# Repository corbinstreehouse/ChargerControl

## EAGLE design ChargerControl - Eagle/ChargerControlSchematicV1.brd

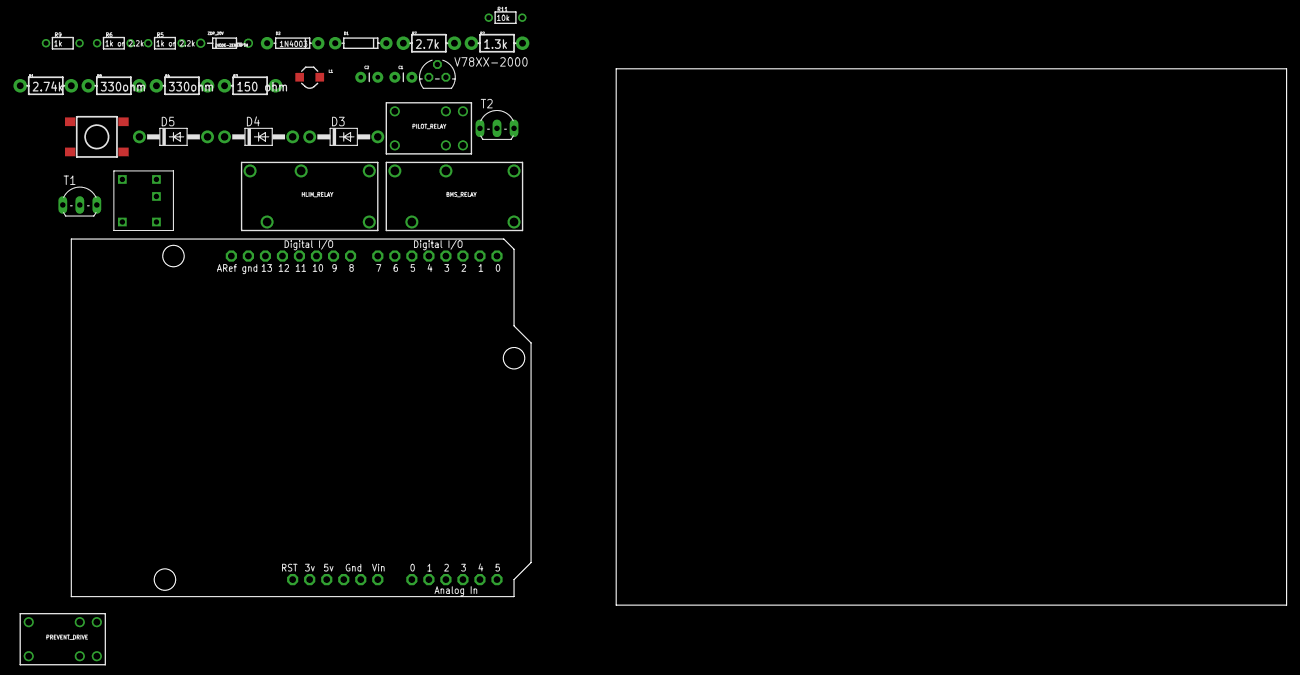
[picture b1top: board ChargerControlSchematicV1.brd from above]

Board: 2 copper layers, 181.3 x 80.0 mm, 29 parts (0 on the bottom side), 21 nets, no tracks yet.

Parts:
BMS_RELAY: RELAYPTH; RELAY-G5Q
C1, C2: 10uF; CAP-PTH-SMALL
D1: DIODE-1N4148
D2: 1N4003; DIODE-1N4148
D3, D4, D5: 1N4004; DO41-10
HLIM_RELAY: RELAYPTH; RELAY-G5Q
L1: 40uH 2amp; CDRH2D09
LATCH_SWITCH: SWITCH-MOMENTARY-2; TACTILE_SWITCH_TALL
PILOT_RELAY: RELAY-2G5Q; RELAY-G5V
PREVENT_DRIVE: RELAY-2G5Q; RELAY-G5V
R1: 2.74k; AXIAL-0.3-KIT
R2: 1.3k; AXIAL-0.3-KIT
R3: 150 ohm; AXIAL-0.3-KIT
R4, R8: 330ohm; AXIAL-0.3-KIT
R5, R6: 1k or 2.2k; 1/6W-RES
R7: 2.7k; AXIAL-0.3-KIT
R9: 1k; 1/6W-RES
R11: 10k; 1/6W-RES
T1, T2: 2N2222; TO92-EBC-OVAL
U$1: POLOLU_PSHBTN_PWR; POLO_PSHBTN_PWR
U$2: ARDUINOUNO; ARDUINO
V78XX-2000: 78L05Z; TO92
ZDP_20V: DIODE-ZENERPTH; DIODE-ZENER

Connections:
240_AC_GND: LATCH_SWITCH.A2, R8.P$1
AC-DC-12V-OUT: U$2.VIN, V78XX-2000.1
CAR_12V+: BMS_RELAY.5, D3.C, D4.C, L1.P$1, PREVENT_DRIVE.2, U$1.P$4, U$1.P$5, ZDP_20V.P$1
GND: C2.2, PREVENT_DRIVE.9, R1.P$2, R7.P$2, T1.E, T2.E, U$1.P$1, V78XX-2000.2, ZDP_20V.P$2
HLIM: D5.A, D5.C, HLIM_RELAY.5, R11.2, U$2.D2
unnamed: U$1.P$2, U$2.GND1
unnamed: R9.1, U$2.D6
unnamed: R6.1, U$2.D4
unnamed: D2.C, R1.P$1, R2.P$1
unnamed: R5.2, T1.B
unnamed: R5.1, U$2.D5
unnamed: R4.P$2, R11.1, U$2.5V
unnamed: D3.A, PILOT_RELAY.9, T1.C
unnamed: BMS_RELAY.1, D4.A, T2.C
unnamed: R6.2, T2.B
unnamed: D1.A, R9.2
unnamed: LATCH_SWITCH.B2, R3.P$2, R8.P$2
unnamed: C2.1, L1.P$2, V78XX-2000.3
PILOT_RELAY: U$1.P$3, U$2.D7
PIN2: D1.C, HLIM_RELAY.2
PROXIMITY: R3.P$1, R4.P$1, R7.P$1, U$2.A0

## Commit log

2012-05-30 lots of work
2012-05-30 More menu work; setting time now works.
2012-06-02 date setting
2012-06-02 added more charging options
2012-06-07 After a lot of project cleanup to not copy files from Arduino
2012-06-09 Added more items in the tree for code completion.
2012-06-09 Implemented a lot of stuff.
2012-06-09 Implemented the timer. Added the ability to set the current time for the RTC.
2012-06-10 ordered parts; implemented scrolling and charging status.
2012-06-10 Allow editing the duration (buggy)
2012-06-12 allow editing balance duration. wrap the menus.
2012-06-20 Add more code to optionally not use a relay for the pilot signal. but it isn't safe to do so w/the manzanita charger.
2012-11-03 Ignore proximity signal code
2012-11-03 new bms waiting state
2012-11-04 New code to turn the charger relay on and off explicitly and not use the BMLS High limit pull down.
2012-11-04 Ignore files *.o
2012-11-06 Lower the proximity check
2012-11-09 Add eagle schematic
2012-11-09 Ignore more eagle files
2012-11-09 Updated build files, and add Leonardo support (not tested though, but it does upload).
2012-11-09 Remove my old file; i'm using git geez
2012-11-09 compile and upload. i like this better. one stop shopping.
2012-11-13 Unfortunately, my EVSE at home goes into “error mode” if it detects the plug is plugged in and the car isn’t charging for X amount of time (not sure what X is). So, to work around that, if we are doi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
2012-11-16 eagle tweaks
2012-11-16 remove unused code
2012-11-17 Revert "Unfortunately, my EVSE at home goes into “error mode” if it detects the plug is plugged in and the car isn’t charging for X amount of time (not sure what X is). So, to work around that, if we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
    This reverts commit 6580267e00a060ff7d8a626078f34422cd39f4f3.
2012-11-17 Show time option added. Fixed the prix test to be "smarter". Use a 5v out signal for the prox test so it isn't always "hot" which was messing up my home EVSE
2012-11-17 Updated board layout.

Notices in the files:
parts and their libraries:
SparkFun: Licensing: CC v3.0 Share-Alike You are welcome to use this library for commercial purposes.
